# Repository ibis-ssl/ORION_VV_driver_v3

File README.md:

# OrionBLDCモータードライバ
こちらに統合 → https://github.com/ChikuwaRobo/KiCAD_Projects.git

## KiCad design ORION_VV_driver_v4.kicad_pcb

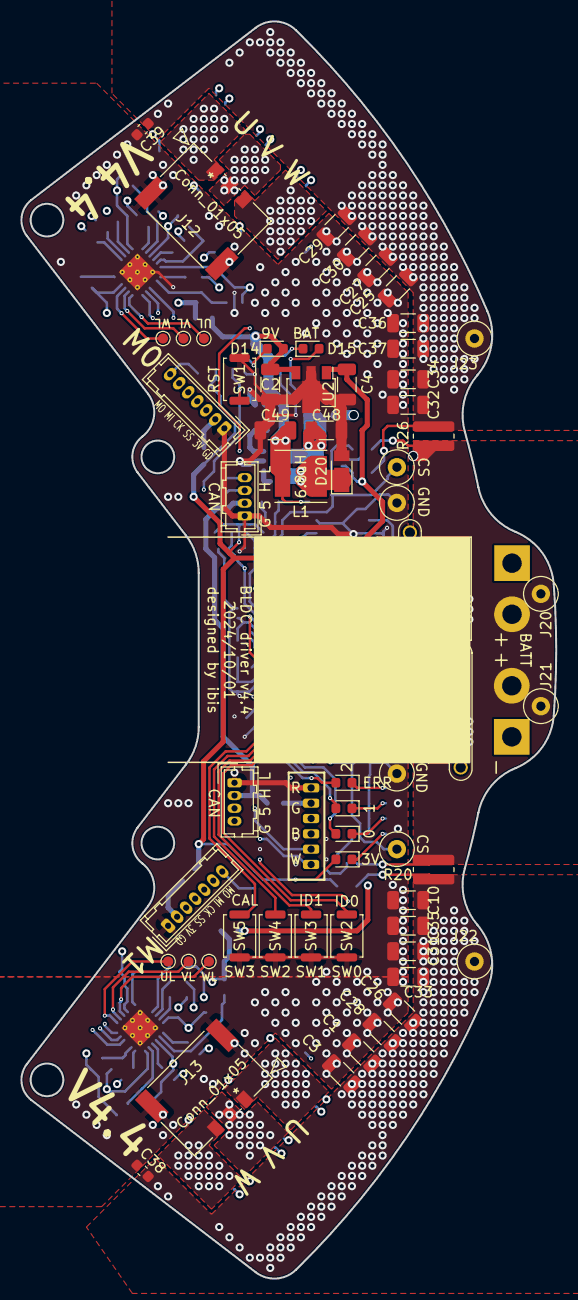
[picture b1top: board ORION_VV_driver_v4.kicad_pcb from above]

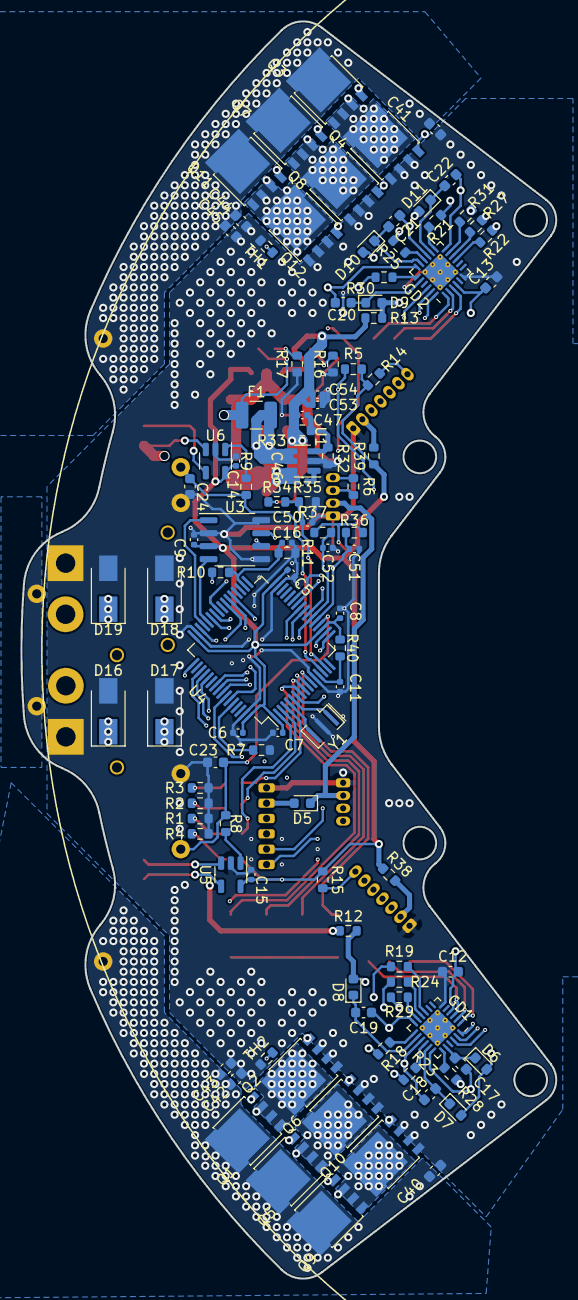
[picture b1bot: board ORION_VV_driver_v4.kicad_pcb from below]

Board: 4 copper layers, 52.4 x 123.1 mm, 165 parts (104 on the bottom side), 105 nets.

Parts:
C1, C2, C3, C4, C10, C25, C26, C27, C28, C29, C30, C31, C32, C33, C34, C35, C36, C37, C48: 4.7u; C_1206_3216Metric
C5, C6, C7, C8, C9, C11, C14, C15, C16, C46, C47, C50, C51, C52, C53, C54: 0.1u; C_0402_1005Metric
C12, C13, C23, C24, C38, C39, C40, C41, C42, C43, C44, C45: 0.1u; C_0603_1608Metric
C17, C18, C19, C20, C21, C22: 1u; C_0603_1608Metric
C49: 10u; C_1206_3216Metric
D1, D2, D3, D4, D14, D15: LED; LED_0603_1608Metric
D5, D6, D7, D8, D9, D10, D11: D; D_0603_1608Metric
D16, D17, D18, D19: D_Zener; D_SMA
D20: D; D_PowerDI-123
F1: Polyfuse; Fuse_1210_3225Metric
GD1, GD2: FD6288Q; HVQFN-24-1EP_4x4mm_P0.5mm_EP2.6x2.6mm_ThermalVias
J1, J7, J8, J9, J10, J14: Conn_01x01; TestPoint_Pad_D1.0mm
J2, J3: Conn_01x04; Hirose_DF13-04P-1.25DSA_1x04_P1.25mm_Vertical
J4: Conn_01x06; ZH_B6B-ZR
J5, J6: Conn_01x07; Hirose_DF13-07P-1.25DSA_1x07_P1.25mm_Vertical
J11: Conn_01x02; AMASS_XT30PW-M_1x02_P2.50mm_Horizontal
J12, J13: Conn_01x05; 2053380003
J15: Conn_01x02; AMASS_XT30PW-F_1x02_P2.50mm_Horizontal
J16, J17, J18, J19, J20, J21, J22, J23: Conn_01x01; TestPoint_Loop_D2.60mm_Drill0.9mm_Beaded
L1: 6.8u; L_Taiyo-Yuden_NR-50xx
Q1, Q2, Q3, Q4, Q5, Q6, Q7, Q8, Q9, Q10, Q11, Q12: IRF8721PBF-1; LFPAK56
R1, R2, R3, R4, R33: 4.7k; R_0603_1608Metric
R5, R7, R11, R35: 1k; R_0603_1608Metric
R6: 120; R_0603_1608Metric
R8, R9: 100; R_0603_1608Metric
R10, R14, R15, R34, R36, R37: 10k; R_0603_1608Metric
R12, R13, R38, R39: 0; R_0603_1608Metric
R16, R17: 47k; R_0603_1608Metric
R18, R19, R21, R22, R23, R24, R25, R27, R28, R29, R30, R31: 10; R_0603_1608Metric
R20, R26: 5m; R_0815_2038Metric
R32: 470; R_0603_1608Metric
R40: 1; R_0603_1608Metric
SW1, SW2, SW3, SW4, SW5: SW_Push; SW_Push_SPST_NO_Alps_SKRK
TH1, TH2: Thermistor; R_0603_1608Metric
U1: BD9G101G; SOT-23-6
U2: L78L33_SOT89; SOT-89-3
U3: MAX3051; SO-8_3.9x4.9mm_P1.27mm
U4: LQFP-64_10x10mm_P0.5mm
U5, U6: ZXCT108x; SOT-23-5
Y1: Resonator; Resonator_SMD_Murata_CSTxExxV-3Pin_3.0x1.1mm

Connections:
+3V3: C4.2, C5.2, C6.2, C7.2, C8.2, C9.2, C14.2, C15.2, D4.2 (A), R5.2, R14.2, R15.2, R36.1, R37.1, R38.1, R39.1, R40.2, U2.1 (OUT), U3.3 (VDD), U4.1 (VBAT), U4.19 (VDD), U4.32 (VDD), U4.48 (VDD), U4.64 (VDD), U5.5 (Vcc), U6.5 (Vcc)
+5V: D5.1 (K), J2.2, J3.2
+9V: C2.2, C47.1, C49.1, C53.1, C54.1, D14.2 (A), L1.2, R12.1, R13.1, R33.2, R34.1, U2.3 (IN)
+24V: C48.1, F1.2, U1.4 (EN), U1.5 (VCC)
+BATT: D15.2 (A), D16.1 (K), D17.1 (K), D18.1 (K), D19.1 (K), F1.1, J11.2, J15.2, J20.1, J21.1, R10.1, R20.1, R26.1, U5.3 (S+), U6.3 (S+)
/BATT_V_SENS: C16.2, R10.2, R11.1, U4.34 (PB13)
/CAN_H: J2.3, J3.3, R6.1, U3.7 (CANH)
/CAN_L: J2.4, J3.4, R6.2, U3.6 (CANL)
/CAN_RX: U3.4 (RXD), U4.44 (PA11)
/CAN_TX: U3.1 (TXD), U4.45 (PA12)
/GD_9V_M0: C13.2, D9.2 (A), D10.2 (A), D11.2 (A), GD2.4 (VCC), R13.2
/GD_9V_M1: C12.2, D6.2 (A), D7.2 (A), D8.2 (A), GD1.4 (VCC), R12.2
/GD_V_SENS: C50.2, R34.2, R35.1, U4.15 (PA1)
/LED_0: D1.2 (A), U4.2 (PC13)
/LED_1: D2.2 (A), U4.3 (PC14)
/LED_2: D3.2 (A), U4.4 (PC15)
/M0_CS: C24.1, J18.1, R9.1, U4.14 (PA0)
/M0_CSL: C25.1, C27.1, C29.1, C30.1, C32.1, C34.1, C36.1, C37.1, C39.2, C41.2, C44.2, C45.2, J23.1, Q3.5 (D), Q7.5 (D), Q11.5 (D), R26.2, U6.4 (S-)
/M0_U: C22.1, GD2.12 (VS3), J12.1, Q3.1 (S), Q3.2 (S), Q3.3 (S), Q4.5 (D)
/M0_UH: GD2.22 (HIN1), U4.41 (PA8)
/M0_UL: GD2.1 (LIN1), J1.1, U4.23 (PA7)
/M0_V: C21.1, GD2.15 (VS2), J12.2, Q7.1 (S), Q7.2 (S), Q7.3 (S), Q8.5 (D)
/M0_VH: GD2.23 (HIN2), U4.42 (PA9)
/M0_VL: GD2.2 (LIN2), J7.1, U4.26 (PB0)
/M0_W: C20.1, GD2.18 (VS1), J12.3, Q11.1 (S), Q11.2 (S), Q11.3 (S), Q12.5 (D)
/M0_WH: GD2.24 (HIN3), U4.43 (PA10)
/M0_WL: GD2.3 (LIN3), J8.1, U4.27 (PB1)
/M1_CS: C23.1, J16.1, R8.1, U4.20 (PA4)
/M1_CSL: C1.1, C3.1, C10.1, C26.1, C28.1, C31.1, C33.1, C35.1, C38.2, C40.2, C42.2, C43.2, J22.1, Q1.5 (D), Q5.5 (D), Q9.5 (D), R20.2, U5.4 (S-)
/M1_U: C19.1, GD1.12 (VS3), J13.1, Q1.1 (S), Q1.2 (S), Q1.3 (S), Q2.5 (D)
/M1_UH: GD1.22 (HIN1), U4.37 (PC6)
/M1_UL: GD1.1 (LIN1), J9.1, U4.51 (PC10)
/M1_V: C18.1, GD1.15 (VS2), J13.2, Q5.1 (S), Q5.2 (S), Q5.3 (S), Q6.5 (D)
/M1_VH: GD1.23 (HIN2), U4.38 (PC7)
/M1_VL: GD1.2 (LIN2), J10.1, U4.52 (PC11)
/M1_W: C17.1, GD1.18 (VS1), J13.3, Q9.1 (S), Q9.2 (S), Q9.3 (S), Q10.5 (D)
/M1_WH: GD1.24 (HIN3), U4.39 (PC8)
/M1_WL: GD1.3 (LIN3), J14.1, U4.53 (PC12)
/NRST: R5.1, SW1.2, U4.7 (NRST)
/NSS_ENC0: J6.3, U4.59 (PB7)
/NSS_ENC1: J5.3, U4.58 (PB6)
/OSC_IN: U4.5 (PF0), Y1.3
/OSC_OUT: U4.6 (PF1), Y1.1
/SPI_CLK: J5.4, J6.4, U4.55 (PB3)
/SPI_MISO: J5.5, J6.5, U4.56 (PB4)
/SPI_MOSI: J5.6, J6.6, U4.57 (PB5)
/SW0: SW2.2, U4.8 (PC0)
/SW1: SW3.2, U4.9 (PC1)
/SW2: SW4.2, U4.10 (PC2)
/SW3: SW5.2, U4.11 (PC3)
/SWCLK: J4.3, U4.49 (PA14)
/SWDIO: J4.4, U4.46 (PA13)
/TEMP_0: J5.7, R15.1, U4.17 (PA3)
/TEMP_1: J6.7, R14.1, U4.18 (PF4)
/TEMP_FET_0: C51.2, R36.2, TH1.1, U4.21 (PA5)
/TEMP_FET_1: C52.2, R37.2, TH2.1, U4.22 (PA6)
/UART1_RX: J4.6, U4.25 (PC5)
/UART1_TX: J4.5, U4.24 (PC4)
GND: C1.2, C2.1, C3.2, C4.1, C5.1, C6.1, C7.1, C8.1, C9.1, C10.2, C11.1, C12.1, C13.1, C14.1, C15.1, C16.1, C23.2, C24.2, C25.2, C26.2, C27.2, C28.2, C29.2, C30.2, C31.2, C32.2, C33.2, C34.2, C35.2, C36.2, C37.2, C38.1, C39.1, C40.1, C41.1, C42.1, C43.1, C44.1, C45.1, C48.2, C49.2, C50.1, C51.1, C52.1, C53.2, C54.2, D16.2 (A), D17.2 (A), D18.2 (A), D19.2 (A), D20.2 (A), GD1.6 (COM), GD1.25 (PAD), GD2.6 (COM), GD2.25 (PAD), J2.1, J3.1, J4.1, J5.1, J6.1, J11.1, J12.4, J12.5, J13.4, J13.5, J15.1, J17.1, J19.1, Q2.1 (S), Q2.2 (S), Q2.3 (S), Q4.1 (S), Q4.2 (S), Q4.3 (S), Q6.1 (S), Q6.2 (S), Q6.3 (S), Q8.1 (S), Q8.2 (S), Q8.3 (S), Q10.1 (S), Q10.2 (S), Q10.3 (S), Q12.1 (S), Q12.2 (S), Q12.3 (S), R1.1, R2.1, R3.1, R4.1, R7.1, R11.2, R16.1, R17.1, R32.1, R35.2, SW1.1, SW2.1, SW3.1, SW4.1, SW5.1, TH1.2, TH2.2, U1.2 (GND), U2.2 (GND), U3.2 (GND), U3.5 (SHDN), U3.8 (RS), U4.12 (VSSA), U4.31 (VSS), U4.47 (VSS), U4.63 (VSS), U5.2 (GND), U6.2 (GND), Y1.2
unnamed: C11.2, R40.1, U4.13 (VDDA)
unnamed: C17.2, D6.1 (K), GD1.20 (VB1)
unnamed: C18.2, D7.1 (K), GD1.17 (VB2)
unnamed: C19.2, D8.1 (K), GD1.14 (VB3)
unnamed: C20.2, D9.1 (K), GD2.20 (VB1)
unnamed: C21.2, D10.1 (K), GD2.17 (VB2)
unnamed: C22.2, D11.1 (K), GD2.14 (VB3)
unnamed: C46.1, D20.1 (K), L1.1, U1.6 (LX)
unnamed: C46.2, U1.1 (BST)
unnamed: C47.2, R32.2, R33.1, U1.3 (FB)
unnamed: D1.1 (K), R1.2
unnamed: D2.1 (K), R2.2
unnamed: D3.1 (K), R3.2
unnamed: D4.1 (K), R4.2
unnamed: D5.2 (A), J4.2
unnamed: D14.1 (K), R16.2
unnamed: D15.1 (K), R17.2
unnamed: GD1.9 (LO3), R19.1
unnamed: GD1.10 (LO2), R24.1
unnamed: GD1.11 (LO1), R29.1
unnamed: GD1.13 (HO3), R18.1
unnamed: GD1.16 (HO2), R23.1
unnamed: GD1.19 (HO1), R28.1
unnamed: GD2.9 (LO3), R22.1
unnamed: GD2.10 (LO2), R27.1
unnamed: GD2.11 (LO1), R31.1
unnamed: GD2.13 (HO3), R21.1
unnamed: GD2.16 (HO2), R25.1
unnamed: GD2.19 (HO1), R30.1
unnamed: J5.2, R38.2
unnamed: J6.2, R39.2
unnamed: Q1.4 (G), R18.2
unnamed: Q2.4 (G), R19.2
unnamed: Q3.4 (G), R21.2
unnamed: Q4.4 (G), R22.2
unnamed: Q5.4 (G), R23.2
unnamed: Q6.4 (G), R24.2
unnamed: Q7.4 (G), R25.2
unnamed: Q8.4 (G), R27.2
unnamed: Q9.4 (G), R28.2
unnamed: Q10.4 (G), R29.2
unnamed: Q11.4 (G), R30.2
unnamed: Q12.4 (G), R31.2
unnamed: R7.2, U4.60 (BOOT0)
unnamed: R8.2, U5.1 (OUT)
unnamed: R9.2, U6.1 (OUT)

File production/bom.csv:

Designator,Footprint,Quantity,Value,LCSC Part #
"C1, C10, C2, C25, C26, C27, C28, C29, C3, C30, C31, C32, C33, C34, C35, C36, C37, C4, C48",C_1206_3216Metric,19,4.7u,
"C11, C14, C15, C16, C46, C47, C5, C50, C51, C52, C6, C7, C8, C9",C_0402_1005Metric,14,0.1u,
"C12, C13, C23, C24, C38, C39, C40, C41, C42, C43, C44, C45",C_0603_1608Metric,12,0.1u,
"C17, C18, C19, C20, C21, C22",C_0603_1608Metric,6,1u,
C49,C_1206_3216Metric,1,10u,
"D1, D14, D15, D2, D3, D4",LED_0603_1608Metric,6,LED,
"D10, D11, D5, D6, D7, D8, D9",D_0603_1608Metric,7,D,
"D16, D17, D18, D19",D_SMA,4,D_Zener,
D20,D_PowerDI-123,1,D,
FB1,R_0603_1608Metric,1,FB100,
"GD1, GD2",HVQFN-24-1EP_4x4mm_P0.5mm_EP2.6x2.6mm_ThermalVias,2,FD6288Q,
"J1, J10, J14, J7, J8, J9",TestPoint_Pad_D1.0mm,6,Conn_01x01,
J11,AMASS_XT30PW-M_1x02_P2.50mm_Horizontal,1,Conn_01x02,
"J12, J13",2053380003,2,Conn_01x05,
J15,AMASS_XT30PW-F_1x02_P2.50mm_Horizontal,1,Conn_01x02,
"J16, J17, J18, J19, J20, J21, J22, J23",TestPoint_Loop_D2.60mm_Drill0.9mm_Beaded,8,Conn_01x01,
"J2, J3",Hirose_DF13-04P-1.25DSA_1x04_P1.25mm_Vertical,2,Conn_01x04,
J4,ZH_B6B-ZR,1,Conn_01x06,
"J5, J6",Hirose_DF13-07P-1.25DSA_1x07_P1.25mm_Vertical,2,Conn_01x07,
L1,L_Taiyo-Yuden_NR-50xx,1,6.8u,
"Q1, Q10, Q11, Q12, Q2, Q3, Q4, Q5, Q6, Q7, Q8, Q9",LFPAK56,12,IRF8721PBF-1,
"R1, R2, R3, R33, R4",R_0603_1608Metric,5,4.7k,
"R10, R14, R15, R34, R36, R37",R_0603_1608Metric,6,10k,
"R11, R35, R5, R7",R_0603_1608Metric,4,1k,
"R16, R17",R_0603_1608Metric,2,47k,
"R18, R19, R21, R22, R23, R24, R25, R27, R28, R29, R30, R31",R_0603_1608Metric,12,10,
"R20, R26",R_0815_2038Metric,2,10m,
R32,R_0603_1608Metric,1,470,
R6,R_0603_1608Metric,1,120,
"R8, R9",R_0603_1608Metric,2,100,
"SW1, SW2, SW3, SW4, SW5",SW_Push_SPST_NO_Alps_SKRK,5,SW_Push,
"TH1, TH2",R_0603_1608Metric,2,Thermistor,
U1,SOT-23-6,1,BD9G101G,
U2,SOT-89-3,1,L78L33_SOT89,
U3,SO-8_3.9x4.9mm_P1.27mm,1,MAX3051,
U4,LQFP-64_10x10mm_P0.5mm,1,~,
"U5, U6",SOT-23-5,2,ZXCT108x,
Y1,Resonator_SMD_Murata_CSTxExxV-3Pin_3.0x1.1mm,1,Resonator,

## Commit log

2022-12-07 ビアうち
2023-02-12 hoge
2023-03-29 v4 init 信号ビアサイズ変更、サーミスタ追加、DCDCをBD9に変更。GDを9V化
2023-03-29 配線とシルクの改善
2023-09-16 シルク追加
2023-09-16 シルクをv4.1に修正
2023-10-19 マイコン位置を変更&再配線中
2023-12-29 外形更新
2024-03-13 DRC通ってるか！？？！？
2024-04-02 パワー系チェック用のテストパッド追加
2024-09-07 エンコーダ電源にFB追加、GD電源に0Ω抵抗追加
2024-09-08 銅線貼り付けパターンの改善
2024-10-01 判別用シルク追加
2024-10-01 シルク調整
2024-11-02 KiCAD8.0に更新
2026-06-08 Add project title and link to GitHub repository

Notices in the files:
parts and their libraries:
Copyright 2021 Accelerated Designs. All rights reserved.
